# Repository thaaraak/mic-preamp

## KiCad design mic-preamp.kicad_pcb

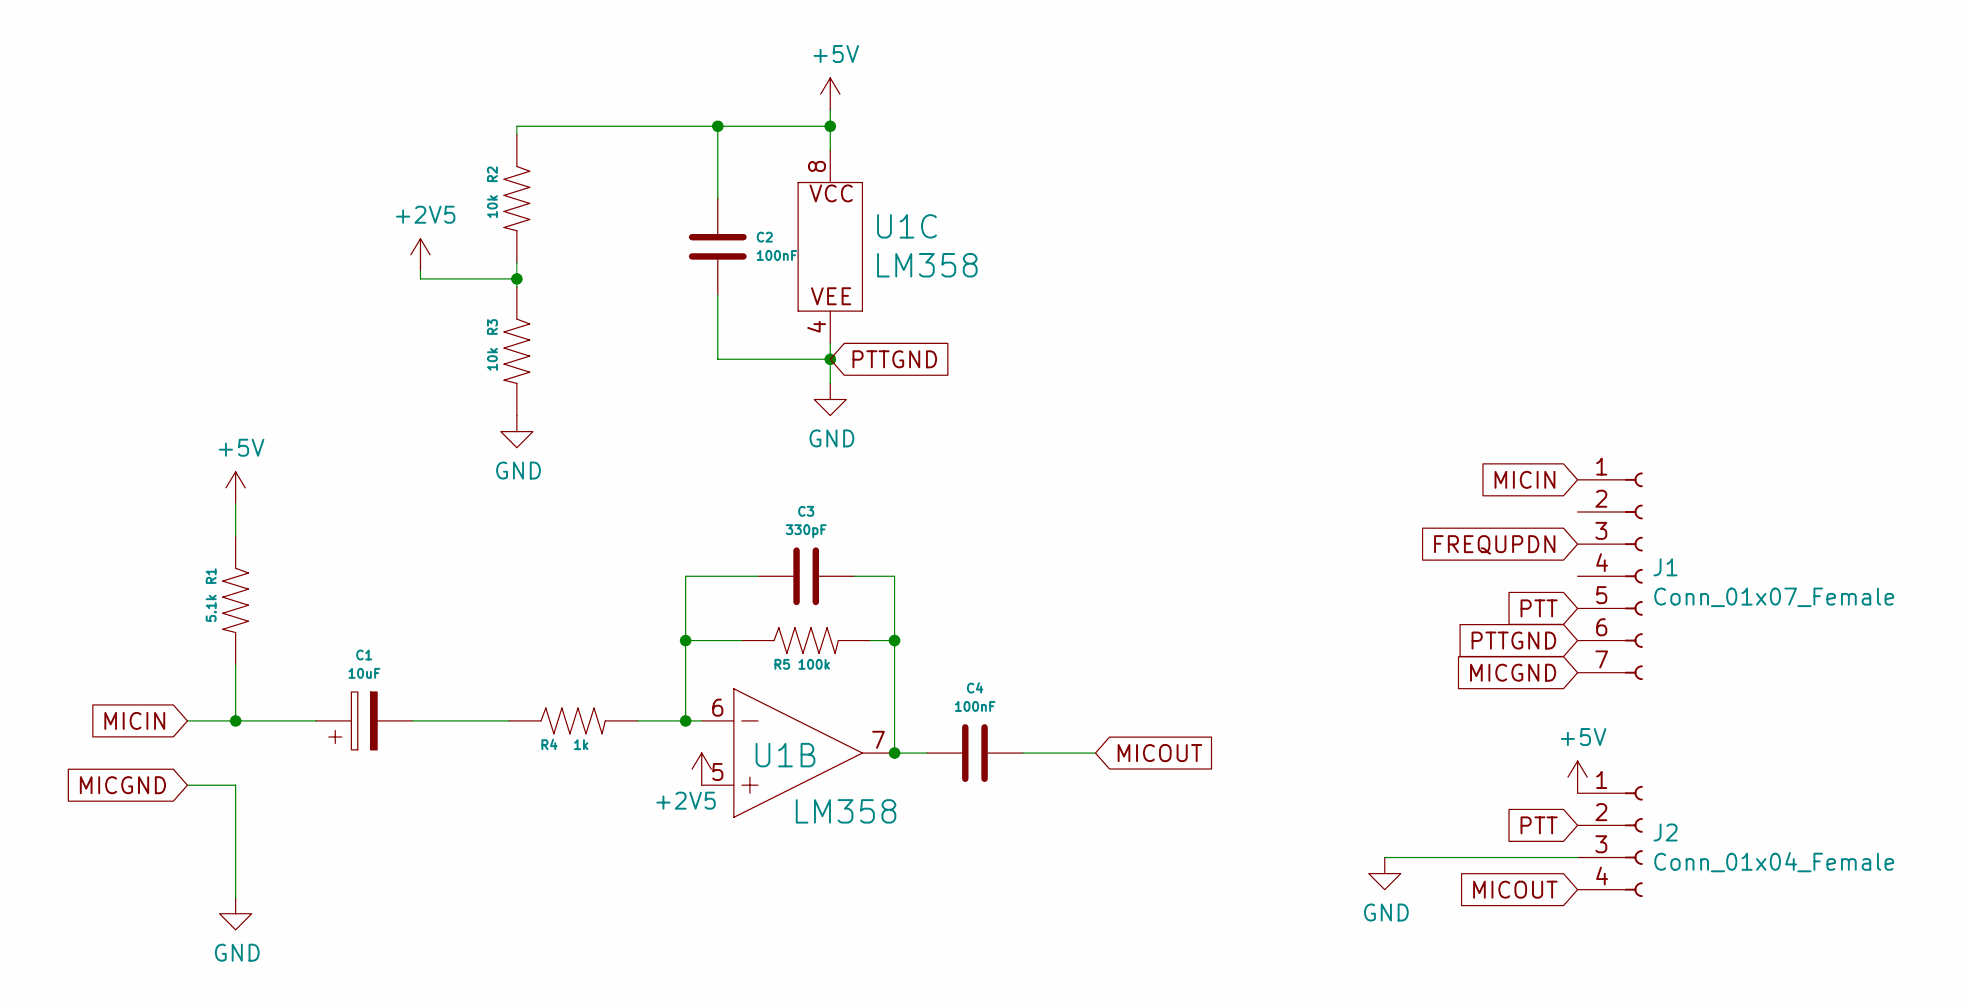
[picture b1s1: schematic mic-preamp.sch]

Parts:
C1: 10uF; CP_Elec_4x5.4
C2, C4: 100nF; Capacitor 1206
C3: 330pF; Capacitor 1206
J1: Conn_01x07_Female; PinHeader_1x07_P2.54mm_Vertical
J2: Conn_01x04_Female; PinHeader_1x04_P2.54mm_Vertical
R1: 5.1k; Resistor 1206
R2, R3: 10k; Resistor 1206
R4: 1k; Resistor 1206
R5: 100k; Resistor 1206
U1: LM358; SOIC8

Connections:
+2V5: R2.2, R3.1, U1.5 (+IN)
+5V: C2.1, J2.1, R1.1, R2.1, U1.8 (P$V+)
FREQUPDN: J1.3
MICGND: C2.2, J1.6, J1.7, J2.3, R3.2, U1.4 (P$V-)
MICIN: C1.1, J1.1, R1.2
MICOUT: C4.1, J2.4
unnamed: C1.2, R4.1
unnamed: C3.1, C4.2, R5.2, U1.7 (OUT)
unnamed: C3.2, R4.2, R5.1, U1.6 (-IN)
PTT: J1.5, J2.2

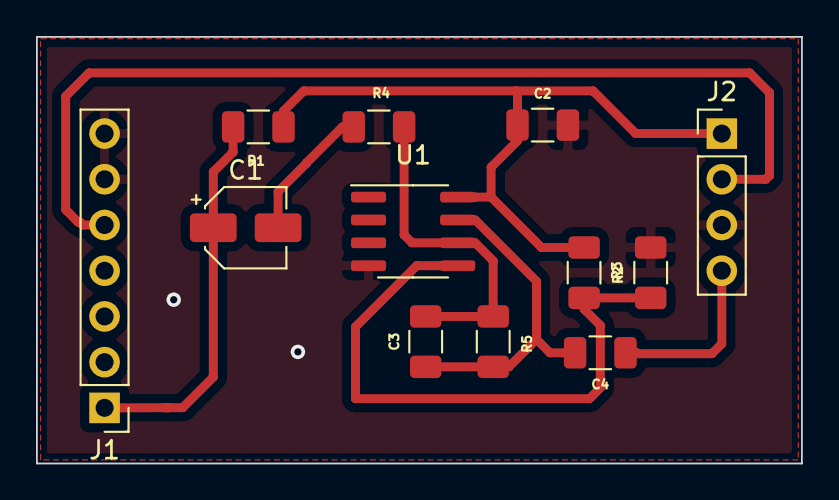
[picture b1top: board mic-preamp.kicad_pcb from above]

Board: 2 copper layers, 42.5 x 23.7 mm, 12 parts (0 on the bottom side), 9 nets.

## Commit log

2022-12-02 added output cap
2022-12-04 330pF
